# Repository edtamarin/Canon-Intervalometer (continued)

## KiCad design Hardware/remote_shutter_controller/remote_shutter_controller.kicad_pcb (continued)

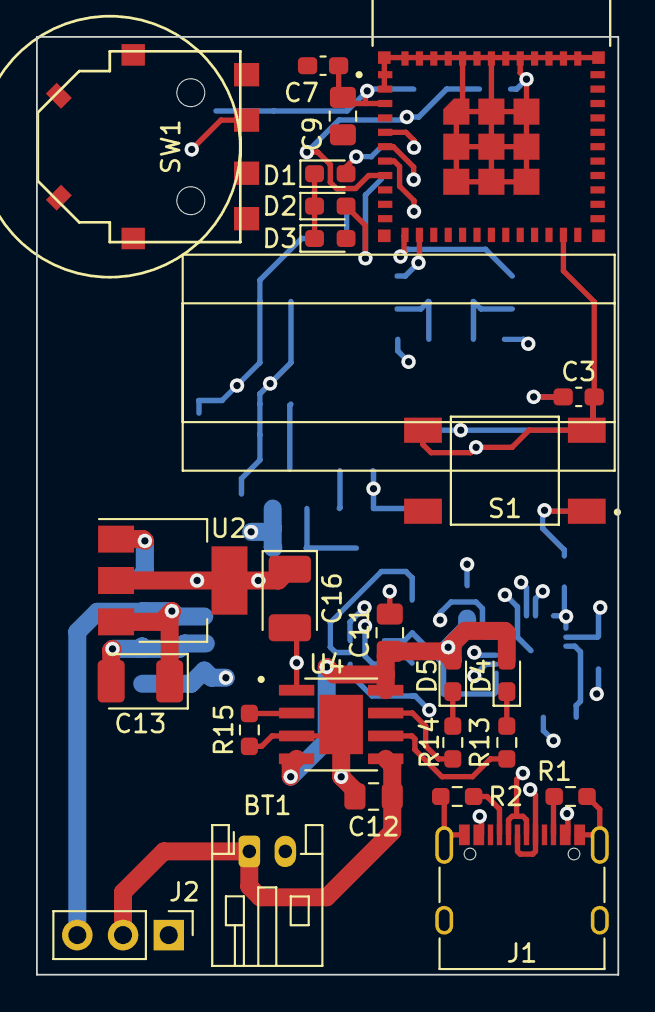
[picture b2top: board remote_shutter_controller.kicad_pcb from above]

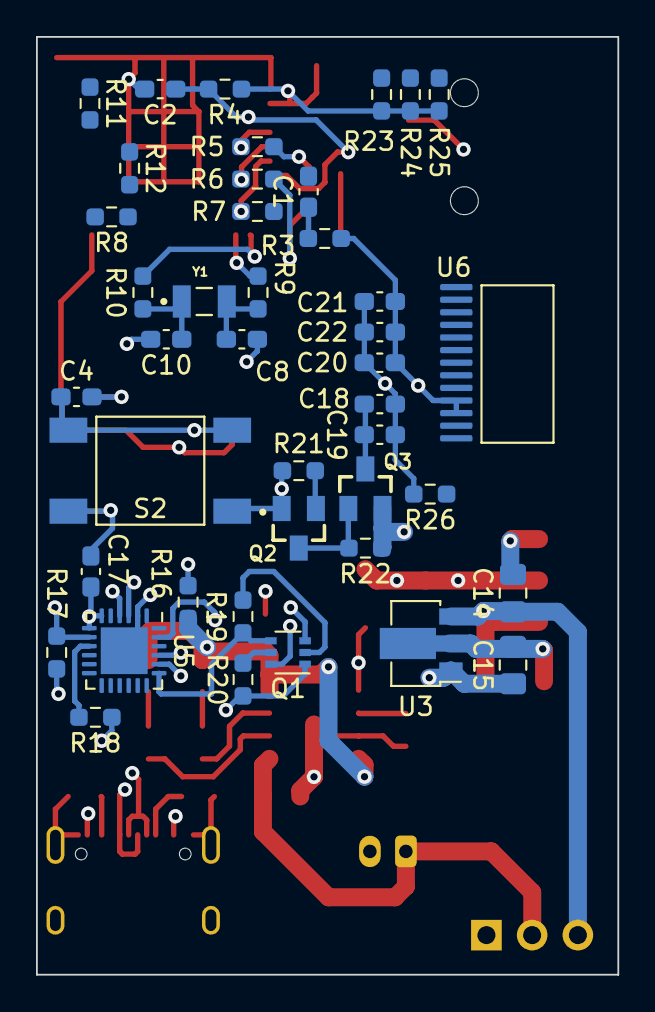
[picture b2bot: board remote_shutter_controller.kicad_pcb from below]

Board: 4 copper layers, 32.3 x 52.1 mm, 67 parts (42 on the bottom side), 46 nets.

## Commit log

2022-11-23 Initial KiCad project
2022-11-23 Initial schematic planning
    Added ESP32, CP2102 and hierarchical sheets.
2022-11-26 Added BOM. Added controls.
    Placed jack, switches, OLED display and rotary encoders.
2022-11-26 Added power & comms.
2022-11-26 Added crystal
2022-11-26 Added missing footprints. First PCB export.
2022-11-26 Fixed bus routing
2022-11-26 Replaced rotary encoders
    Now one flat to save space.
2022-11-26 Started routing. Added power switch.
2022-11-27 Added LiIon charge circuit
2022-11-27 Routing USB and charger.
2022-11-27 Removed redundant pullups
2022-11-27 Further routing. Fixed I2C net connection.
2022-11-27 Initial routing complete
2022-11-27 Added logo. Changed RST route.
2022-11-27 Fixed cap placement
    C11 and C12 were placed under the battery
2022-11-27 Fixed jack pinout
2022-11-27 DRC error fixes.
2022-11-27 Added initial Arduino software project
2022-12-04 Fixed via sizes. Added IO0 pullup.
2022-12-04 Added controller project.
2022-12-05 Work on the controller
2022-12-25 Work on the controller PCB
2023-01-10 Schematic updates. First export to PCB
    Added 9V line, OLED switch circuit. Added OLED footprint.
2023-01-21 Started layout, replaced footprint for battery connector
2023-01-21 Further layout work
2023-01-21 Layout pre-routing
2023-01-23 Initial routing.
2023-04-02 Added debug connectors
2023-04-02 Updated routing, ground plane now empty
2023-04-02 More routing updates
2023-04-07 Small updates
2023-05-06 Changing layout & updated ESP footprint
2023-05-07 Changed layout for better routing. New routing.
2023-05-07 Fixed DRC issues. Updated revision number
